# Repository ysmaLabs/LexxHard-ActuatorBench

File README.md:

# LexxHard-ActuatorBench
Electronics part of the actuator bench

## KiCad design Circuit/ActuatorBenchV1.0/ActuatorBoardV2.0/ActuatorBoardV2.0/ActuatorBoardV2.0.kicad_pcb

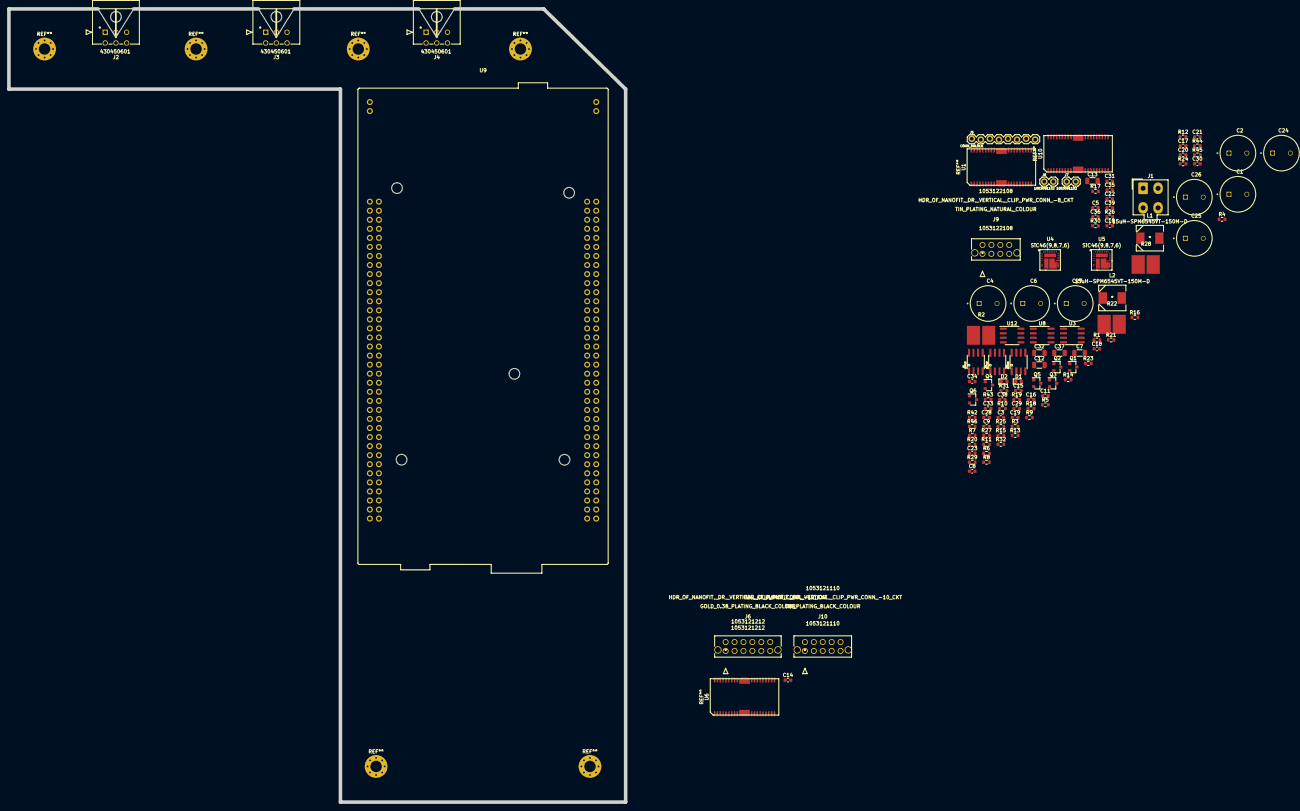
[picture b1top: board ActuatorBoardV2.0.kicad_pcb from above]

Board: 2 copper layers, 173.0 x 222.5 mm, 108 parts (0 on the bottom side), 83 nets.

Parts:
C1, C2, C4, C6, C24, C25, C26, C27: 100uF; EEHAZS1J101B
C3, C16, C17, C19, C20, C30, C35: 0.1uF; C_0603_1608Metric
C5, C10, C11, C31, C36: 10uF - 35V; C_0603_1608Metric
C7, C12, C13, C32, C37: 10uF - 50V; C_1206_3216Metric
C8, C9: 1uF; C_0603_1608Metric
C14, C15: 4.7uF; C_0603_1608Metric
C18, C21, C33, C34, C38, C39: Option; C_0603_1608Metric
C22, C23: 33nF; C_0603_1608Metric
C28, C29: 10uF; C_0603_1608Metric
D1, D2: Red - APG1608SURKC/T - LTST-C194KRKT; LED_0603_1608Metric
J1: 39281043
J2, J3, J4: 430450601
J5: CONN_08LOCK; 1X08_LOCK
J6: 1053121212
J7, J8: 1053091102; 1X02
J9: 1053122108
J10: 1053121110
L1, L2: 15uH-SPM6545VT-150M-D; SPM6545VT-150M-D
Q1, Q2, Q3, Q4, Q5, Q6: DMN2075U - SSM3K329R; SOT-23
R1, R11, R12, R16, R18, R21, R27, R42, R43, R44, R45, R46: 10k; R_0603_1608Metric
R2, R22, R28: 0.1ohm-WSHP2818R1000FEA; WSHP2818R1000FEA
R3, R4, R23, R24, R29, R30: 12k; R_0603_1608Metric
R5, R19, R20, R25, R31: 200ohms; R_0603_1608Metric
R6, R26, R32: 100ohms; R_0603_1608Metric
R7, R8: 301k; R_0603_1608Metric
R9, R10: 3.3; R_0603_1608Metric
R13: 57.6k; R_0603_1608Metric
R14: 87.7k; R_0603_1608Metric
R15: 31.2k; R_0603_1608Metric
R17: 52.5k; R_0603_1608Metric
U1, U6, U10: BD63150AFM
U2, U7, U11: ADT7410
U3, U8, U12: INA240A1D; SOIC-8_3.9x4.9mm_P1.27mm
U4, U5: SiC46(9,8,7,6); SIC466ED-T1-GE3
U9: NUCLEO144-F746ZG; ST_Morpho_Connector_144_STLink_MountingHoles

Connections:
3.3V: C24.1, C26.1, C28.1, J5.2, J6.1, J9.5, J9.6, J10.6, J10.7, J10.8, J10.9, L1.2, R1.2, R3.2, R15.2, R19.2, R21.2, R23.2, R27.2, R29.2, R45.2, R46.2, U2.8 (VDD), U3.6 (V+), U4.20 (VOUT), U7.4 (A1), U7.8 (VDD), U8.6 (V+), U9.12 (IOREF), U9.16 (+3V3), U11.3 (A0), U11.8 (VDD), U12.6 (V+)
3.3vPGOOD: R11.1, U4.2 (PGOOD), U9.96 (PB1)
5V: C25.1, C27.1, C29.1, J2.3, J3.3, J4.3, L2.2, R17.2, R20.2, U5.20 (VOUT)
5vPGOOD: R12.1, U5.2 (PGOOD), U9.94 (PB2)
BLK_Screen: J5.8, J6.8, U9.41 (PD5)
CLK_Encoder: J6.9, U9.115 (PD12)
CS_Screen: J5.7, J6.7, U9.118 (PD14)
DC_Screen: J5.6, J6.6, U9.120 (PD15)
DT_Encoder: J6.10, U9.113 (PD13)
DownSignal: J8.1, J9.4, U9.108 (PF5)
EncoderSwitch: J6.11, U9.47 (PE3)
Encoder_CenterActuator_TIM4_CH1: J3.6, U9.28 (ETH_REF_CLK/PA0)
Encoder_CenterActuator_TIM4_CH2: J3.5, U9.30 (ETH_MDIO/PA1)
Encoder_LeftActuator_TIM3_CH1: J2.6, U9.124 (PE9)
Encoder_LeftActuator_TIM3_CH2: J2.5, U9.128 (PE11)
Encoder_RightActuator_TIM1_CH1: J4.6, U9.99 (PB4)
Encoder_RightActuator_TIM1_CH2: J4.5, U9.101 (PB5)
FAIL_Center: R21.1, U6.16 (FAILA)
FAIL_Left: R1.1, U1.16 (FAILA)
FAIL_Right: R27.1, U10.16 (FAILA)
IN1_MOTOR_Center: U6.11 (IN1), U9.50 (PE5)
IN1_MOTOR_Left: U1.11 (IN1), U9.100 (LD3/PB14)
IN1_MOTOR_Right: U9.76 (PC6), U10.11 (IN1)
IN2_MOTOR_Center: U6.12 (IN2), U9.62 (PE6)
IN2_MOTOR_Left: U1.12 (IN2), U9.98 (PB15)
IN2_MOTOR_Right: U9.91 (PC7), U10.12 (IN2)
MOTOR_Center_M: J3.2, U6.6 (OUT2), U6.7 (OUT2), U6.8 (OUT2)
MOTOR_Center_P: J3.1, U6.1 (OUT1), U6.2 (OUT1), U6.3 (OUT1)
MOTOR_Left_M: J2.2, U1.6 (OUT2), U1.7 (OUT2), U1.8 (OUT2)
MOTOR_Left_P: J2.1, U1.1 (OUT1), U1.2 (OUT1), U1.3 (OUT1)
MOTOR_Right_M: J4.2, U10.6 (OUT2), U10.7 (OUT2), U10.8 (OUT2)
MOTOR_Right_P: J4.1, U10.1 (OUT1), U10.2 (OUT1), U10.3 (OUT1)
MicroControllerDOWNSignal: Q2.1 (G), U9.110 (PF4)
MicroControllerSTATE1Signal: Q3.1 (G), U9.82 (STLINK_TX/PD8)
MicroControllerSTATE2Signal: Q4.1 (G), U9.84 (USB_DP/PA12)
MicroControllerSTATE3Signal: Q5.1 (G), U9.86 (USB_DM/PA11)
MicroControllerSTATE4Signal: Q6.1 (G), U9.88 (PB12)
MicroControllerUPSignal: Q1.1 (G), U9.114 (PF10)
Motor_Center_TempSense_SCL: R46.1, U2.1 (SCL), U7.1 (SCL), U9.122 (PF14), U11.1 (SCL)
Motor_Center_TempSense_SDA: R45.1, U2.2 (SDA), U7.2 (SDA), U9.132 (PF15), U11.2 (SDA)
unnamed: C14.2, U4.16 (VDRV)
unnamed: C15.2, U5.16 (VDRV)
unnamed: C18.1, R5.1, R6.2, U3.8 (+)
unnamed: C19.1, U4.4 (BOOT)
unnamed: C19.2, R9.2
unnamed: C20.1, U5.4 (BOOT)
unnamed: C20.2, R10.2
unnamed: C22.2, U4.19 (SS)
unnamed: C23.2, U5.19 (SS)
unnamed: C33.1, R25.1, R26.2, U8.8 (+)
unnamed: C38.1, R31.1, R32.2, U12.8 (+)
unnamed: D1.2 (A), R19.1
unnamed: D2.2 (A), R20.1
unnamed: L1.1, U4.12 (SW), U4.13 (SW), U4.14 (SW)
unnamed: L2.1, U5.12 (SW), U5.13 (SW), U5.14 (SW)
unnamed: R7.1, U4.27 (MODE)
unnamed: R8.1, U5.27 (MODE)
unnamed: R9.1, U4.5 (PHASE), U4.6 (PHASE)
unnamed: R10.1, U5.5 (PHASE), U5.6 (PHASE)
unnamed: R13.1, U4.24 (FSW)
unnamed: R14.1, U5.24 (FSW)
OUTPUT_ADC_MC: C34.1, U8.5, U9.109 (PA3)
OUTPUT_ADC_ML: C21.1, U3.5, U9.107 (PA2)
OUTPUT_ADC_MR: C39.1, U9.32 (PA4), U12.5
PGND: C1.2, C2.2, C3.2, C4.2, C5.2, C6.2, C7.2, C8.2, C9.2, C10.2, C11.2, C12.2, C13.2, C14.1, C15.1, C16.2, C17.2, C18.2, C21.2, C22.1, C23.1, C24.2, C25.2, C26.2, C27.2, C28.2, C29.2, C30.2, C31.2, C32.2, C33.2, C34.2, C35.2, C36.2, C37.2, C38.2, C39.2, D1.1 (K), D2.1 (K), J1.1, J1.2, J2.4, J3.4, J4.4, J5.1, J6.2, J6.12, J6.P1, J6.P2, J7.2, J8.2, J9.7, J9.8, J9.P1, J9.P2, J10.P1, J10.P2, Q1.2 (S), Q2.2 (S), Q3.2 (S), Q4.2 (S), Q5.2 (S), Q6.2 (S), R2.1, R4.1, R6.1, R7.2, R8.2, R13.2, R14.2, R16.1, R18.1, R22.1, R24.1, R26.1, R28.1, R30.1, R32.1, R42.1, R43.1, R44.1, U1.0 (FIN), U1.15 (TEST), U1.18 (TEST1), U1.22 (GND), U1.29 (GND), U2.3 (A0), U2.4 (A1), U2.7 (GND), U3.1 (-), U3.2 (GND), U3.3 (REF2), U3.4 (GND), U3.7 (REF1), U4.9 (PGND), U4.10 (PGND), U4.11 (PGND), U4.17 (PGND), U4.23 (AGND), U4.28 (AGND), U4.30 (PGND), U5.9 (PGND), U5.10 (PGND), U5.11 (PGND), U5.17 (PGND), U5.23 (AGND), U5.28 (AGND), U5.30 (PGND), U6.0 (FIN), U6.15 (TEST), U6.18 (TEST1), U6.22 (GND), U6.29 (GND), U7.3 (A0), U7.7 (GND), U8.1 (-), U8.2 (GND), U8.3 (REF2), U8.4 (GND), U8.7 (REF1), U9.8 (GND), U9.19 (GND), U9.20 (GND), U9.22 (GND), U9.49 (GND), U9.60 (GND), U9.71 (GND), U9.72 (GND), U9.81 (GND), U9.92 (GND), U9.104 (AGND), U9.111 (GND), U9.126 (GND), U9.135 (GND), U9.143 (GND), U9.144 (GND), U10.0 (FIN), U10.15 (TEST), U10.18 (TEST1), U10.22 (GND), U10.29 (GND), U11.4 (A1), U11.7 (GND), U12.1 (-), U12.2 (GND), U12.3 (REF2), U12.4 (GND), U12.7 (REF1)
PS_Center: R44.2, U6.13 (PS), U9.125 (PE15)
PS_Left: R42.2, U1.13 (PS), U9.123 (PE14)
PS_Right: R43.2, U9.127 (PE13), U10.13 (PS)
RES_Screen: J5.5, J6.5, U9.131 (PF12)
RNF_Center: R22.2, R25.2, U6.32 (RNFS), U6.33 (RNF), U6.34 (RNF), U6.35 (RNF)
RNF_Left: R2.2, R5.2, U1.32 (RNFS), U1.33 (RNF), U1.34 (RNF), U1.35 (RNF)
RNF_Right: R28.2, R31.2, U10.32 (RNFS), U10.33 (RNF), U10.34 (RNF), U10.35 (RNF)
SCL_Screen: J5.3, J6.3, U9.83 (PA5)
SDA_Screen: J5.4, J6.4, U9.87 (ETH_CRS_DV/PA7)
UpSignal: J7.1, J9.3, U9.112 (PE8)
VBAT: C1.1, C2.1, C3.1, C4.1, C5.1, C6.1, C7.1, C10.1, C11.1, C12.1, C13.1, C16.1, C17.1, C30.1, C31.1, C32.1, C35.1, C36.1, C37.1, J1.3, J1.4, U1.24 (Vcc), U1.25 (Vcc), U1.26 (Vcc), U4.1 (VCIN), U4.3 (EN), U4.7 (VIN), U4.8 (VIN), U4.29 (VIN), U5.1 (VCIN), U5.3 (EN), U5.7 (VIN), U5.8 (VIN), U5.29 (VIN), U6.24 (Vcc), U6.25 (Vcc), U6.26 (Vcc), U10.24 (Vcc), U10.25 (Vcc), U10.26 (Vcc)
VDD_3.3V: C8.1, R11.2, U4.25 (ILIMIT), U4.26 (VDD)
VDD_5V: C9.1, R12.2, U5.25 (ILIMIT), U5.26 (VDD)
VFB_3.3V: R15.1, R16.2, U4.22 (VFB)
VFB_5v: R17.1, R18.2
VREF_Center: R23.1, R24.2, U6.20 (VREF)
VREF_Left: R3.1, R4.2, U1.20 (VREF)
VREF_Right: R29.1, R30.2, U10.20 (VREF)

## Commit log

2022-09-08 Create Bills&Receipts

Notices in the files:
parts and their libraries:
Copyright 2021 Accelerated Designs. All rights reserved.
